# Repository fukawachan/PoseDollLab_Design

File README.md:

# PoseDoll 人偶硬件设计

Manny / Quinn 传感器可动人偶的独立设计仓库。原来位于 `DollSimulation` UE 工程中的硬件、固件与硬件诊断工具已经迁入本目录；UE 插件、角色资产与完整 Python 模拟器留在原项目。

## 当前状态

本次审查同时评估用户新明确的“摆稳后采集、无需实时动捕”场景：[放宽实时指标后的优化任务](Hardware/PoseDoll44/docs/NEXT_REVIEW_STATIC_CAPTURE.zh-CN.md)。Rev O3 当前代码与封存证据保留原时序，低频/触发式架构尚待审查实施。

- **当前推进为 Rev O 第三轮**：[本轮设计、验证与剩余问题](Hardware/PoseDoll44/docs/START_HERE_REVO3.zh-CN.md)。已实现一体板托、外耳钢背摩擦件和磨损状态检查；修正载荷/质量账、时序统计与节点恢复；生成顶入/侧入板件候选。**整机 1.2 kg 已改为非强制偏好**，尺寸、手感和精度要求保留。完整多轴总装与制造门槛尚未闭合。[第三轮审查入口](Hardware/PoseDoll44/docs/REVIEW_REQUEST_REVO3.zh-CN.md)。

- **历史检查点：Rev O 第二轮**：[本轮设计、验证与缺口](Hardware/PoseDoll44/docs/START_HERE_REVO2.zh-CN.md)。已重构 L6 承力/装配、生成 N3/N4 拆板候选并修复入网调度；完整板位、质量目标和物理门槛仍待闭合。**[给 GPT-6 Pro 的第二轮审查说明](Hardware/PoseDoll44/docs/REVIEW_REQUEST_REVO2.zh-CN.md)** 已整理好源码、证据和重点问题。下列 Rev O 审查入口保留为第一轮历史。

- **历史检查点：Rev O Desktop 初轮**：48 cm 为研究锚点，比较 42/45 cm 及较大后备档；已交付双角色布局、三档关节、原生电气布局和七角色固件。板位、预紧和质量预算仍未达标，完整总装尚未完成。
- **约 91 cm 的 Rev M/N1 为备用**：原文件与旧输出保留，以哈希清单冻结。新旧源码、报告和导出分目录保存。
- 第一轮历史入口：[Rev O 当前结果与失败清单](Hardware/PoseDoll44/docs/START_HERE_REVO.zh-CN.md)。
- **第一轮历史独立审查入口：[给 GPT-6 Pro 的审查说明](Hardware/PoseDoll44/docs/REVIEW_REQUEST_REVO.zh-CN.md)**，包含已知失败、证据链接与下一轮修改要求。

以下为备用版的历史基线：

- **机械基线为 Rev N1**：两款分别按 UE 人物参考比例设计，参考身高约 91 cm；胸前大挡板已取消，左肩局部刮碰已修正。
- **下一项为“局部采集 + 外置电源/USB 接口盒”**：方向已确定，新电路板、安装结构和线束尚未实施。
- **小型化仍待比较**：当前尺寸不是已证明的下限，不能直接缩放现有文件，也不能认定重新设计的小型关节必然昂贵。
- 44 个协议槽中，41 轴测量，骨盆 3 轴固定参考；整体位置和全部整体旋转在 UE 调整。
- 当前交付是数字原型候选，尚未实物鉴定。

## 阅读入口

0. [当前主方案 Rev O3](Hardware/PoseDoll44/docs/START_HERE_REVO3.zh-CN.md)；使用 `scripts/run_revo3.py --run-id <唯一编号>` 复跑，`scripts/Start-Viewer.ps1 -Revision revO3` 查看。以下 Rev M/N 文档用于备用版。

1. [最新 Rev N1 设计入口](Hardware/PoseDoll44/START_HERE_REVN.zh-CN.md)
2. [胸部修订与设备外置方案](Hardware/PoseDoll44/docs/CHEST_AND_EXTERNAL_REVN.zh-CN.md)
3. [尺寸、磁铁和关节小型化评估](Hardware/PoseDoll44/docs/SIZE_REVIEW_BEFORE_EXTERNAL.zh-CN.md)
4. [制造说明](Hardware/PoseDoll44/docs/FABRICATION_REVM.zh-CN.md)、[装配说明](Hardware/PoseDoll44/docs/ASSEMBLY_REVM.zh-CN.md)、[测试和校准](Hardware/PoseDoll44/docs/BUILD_AND_CALIBRATE_REVM.zh-CN.md)
5. [迁移记录和验证](docs/MIGRATION.zh-CN.md)

Rev M 文档描述原完整基线，使用时应应用 Rev N1 的取消件和左肩修订。更早版本与 `planning/` 是历史依据，不能混作当前制造说明。

## 目录组织

| 路径 | 用途 |
|---|---|
| `Hardware/PoseDoll44/cad/` | 参数化机械模型，保留当前模型仍引用的历史模块 |
| `Hardware/PoseDoll44/electronics/` | 原生 KiCad 工程、符号/封装及板级 STEP 输入 |
| `Hardware/PoseDoll44/mechanical_manifest/` | 轴、接口、比例和网络定义 |
| `Hardware/PoseDoll44/docs/`、`verification/` | 设计说明、数字检查和原型验收依据 |
| `Hardware/PoseDoll44/generated/` | 总装、打印件、查看器、交付清单和本地 CAD 缓存 |
| `Hardware/PoseDoll44/reference/`、`references/` | UE 参考数据及元件资料 |
| `Hardware/PoseDoll44/harness/` | 两款线束与下料表 |
| `Firmware/PoseDollFullBody/` | 六节点完整固件与主机端 C 核心测试 |
| `Firmware/PoseDollHardware/` | 早期单关节固件，历史用途 |
| `Tools/PoseDollHardwareBridge/` | 诊断、校准、数据转换和测试 |
| `Tools/PoseDollSimulator/`、`Shared/` | 硬件需要的协议/运动学代码及配置快照，不含模拟器 GUI |
| `planning/` | 原始规划包副本，父目录中的原下载包也保留 |
| `scripts/` | 独立仓库的检查、构建和查看器入口 |
| `.local/` | 本机迁移清单、运行结果等，不入 Git |

保留 `Hardware/`、`Firmware/`、`Tools/` 层级，以保持已有相对路径及历史资料的可追溯性。协议快照来源与逐文件哈希见 [software_snapshot.json](docs/software_snapshot.json)。

## 环境与离线检查

在本目录打开 PowerShell。本机已经建立独立 `.venv`；新克隆可执行：

```powershell
py -3.13 -m venv .venv
.\.venv\Scripts\python.exe -m pip install -r requirements.txt
.\.venv\Scripts\python.exe scripts/check_repository.py
.\scripts\Build-Design.ps1 -Stage OfflineTests
```

离线检查包括协议配置、Python 测试、C 核心测试和 C/Python 数据帧一致性；不连接硬件或操作 UE。C 测试需要 Visual Studio C 工具链，`-VcVars` 可指定 `vcvars64.bat`。本机迁移后结果为 **81 个 Python 测试、9 个 C 场景通过，数据帧逐字节一致**。

## 打开三维查看器

```powershell
.\scripts\Start-Viewer.ps1
```

默认根据 `verification/revO3/latest.json` 打开 Rev O3 查看器，当前为 `http://127.0.0.1:8874/generated/revO3/runs/o3_20260924_r3/review.html`；通过 `-Revision revN` 打开 91 cm 备用版，仅绑定本机。`-NoBrowser` 只启动服务；端口冲突时可用 `-Port` 指定另一端口，不会自动终止其他进程。

Rev O3 的当前及历史检查运行、HTML、网格、STEP、原生 KiCad 板件、固件产物与原始日志随本次审查提交收录；宿主 C 编译产物通过逐件哈希的 portable ZIP 保存。Rev O 第一轮的 HTML、轻量网格、布局数据及三档关节 STEP 也保留。十份体型布局 STEP 下载需先用 `Build-RevO.ps1 -Stage CAD` 重建。91 cm 备用查看器仍依赖未纳入 Git 的大型网格，需复制旧输出或重建。

## CAD、电路和固件

- CAD：CadQuery 2.7。现有 `Hardware/PoseDoll44/tools/run_cad.py` 可使用本机 CQ-editor 2.7 的环境，需要 CQ-editor 保持开启、Python 版本匹配；也可自行安装常规 CadQuery 环境。
- 电路：KiCad 10，打开 `electronics/` 中对应 `.kicad_pro`。搬迁前已打开的 CQ-editor/KiCad 文件，应从新目录重新打开，避免保存回原路径。
- 固件：ESP-IDF 6.1、ESP32-S3。旧构建缓存已保留，但含旧绝对路径；不要直接在其中增量构建。
- 布线工具：Freerouting 2.4.1 JAR 保留在本机 `Hardware/PoseDoll44/tools/vendor/`，不入 Git；许可证与说明保留。

```powershell
.\scripts\Build-Design.ps1 -Stage CAD
.\scripts\Build-Design.ps1 -Stage Firmware
```

CAD 阶段生成/复核 Rev M 完整基线，耗时较长。Rev N1 的修订脚本位于 `cad/revN/`，依赖 Rev M 完整输出及其复核结果，不是上述命令自动生成的另一套角色。当前源码与必要 CAD 输入纳入 Git。

新构建入口使用本仓库 `.venv`。Firmware 阶段会把检测到旧工程路径的节点缓存移入 `.local/legacy-firmware-builds/` 后重新构建，不删除缓存、不烧录。旧脚本中的 CQ-editor、KiCad、ESP-IDF 安装盘符仍是本机配置；换电脑须配置工具路径，历史工具可参考 `local_toolchain.example.json`。UE 参考重新导出需要原 UE 工程及插件，但导出脚本现在将数据写到本设计仓库。

## Git 与本地成果

Git 收录设计源码、KiCad 工程、固件、必要板级 STEP/角色参考输入、协议快照、说明、交付元数据和检查记录。`.gitattributes` 保留原行尾，避免检出时破坏来源文件的字节哈希。

大型总装 STEP、查看器大网格、CAD 缓存、ESP-IDF 构建目录、Python 环境和第三方工具二进制保留在磁盘，由 `.gitignore` 排除；没有启用 Git LFS。Rev O 审查快照额外收录三档单关节总成 STEP、两个 A 级配合样片 STEP/STL、轻量查看器与本轮原始编译/ERC/DRC 日志，Rev O3 本次另显式收录三个检查运行及其可追溯产物，仍未放开其他版本的整个生成目录。其他机器如需完整本地成果，应另外复制 `Hardware/PoseDoll44/generated/`。**推送 Git 不等于备份全部 6.87 GB 本地成果。**

现有验证报告保留为历史快照，迁移后的路径修复和检查另列记录；没有把迁移当成新一轮全身工程验证。本轮提交由使用者推送到远端；审查应指定 `design/revO-desktop-external` 分支和所读取的完整提交号。

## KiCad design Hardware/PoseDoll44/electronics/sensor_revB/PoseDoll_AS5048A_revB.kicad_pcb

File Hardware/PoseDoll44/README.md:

# PoseDoll Manny / Quinn hardware design

[Repository README](../../README.md) · [Rev N1 entry](START_HERE_REVN.zh-CN.md) · [Size review](docs/SIZE_REVIEW_BEFORE_EXTERNAL.zh-CN.md)

Current mechanical candidate: Rev N1 (Rev M full body, chest facade removed, left shoulder clearance corrected). Rear electronics remain integrated; local acquisition plus an external interface box is authorized but not implemented. Miniaturization feasibility and cost are unresolved.

CAD source: `cad/revM/final_model.py` plus `cad/revN/chest_clearance.py`. Historical revisions remain because current code and input provenance refer to them. Use revision manifests rather than mixing standalone exports.

This is a digital prototype candidate, not a manufacturing release or a physically qualified product. See the repository README for the migrated layout, toolchain, ignored local exports, offline checks and viewer startup.

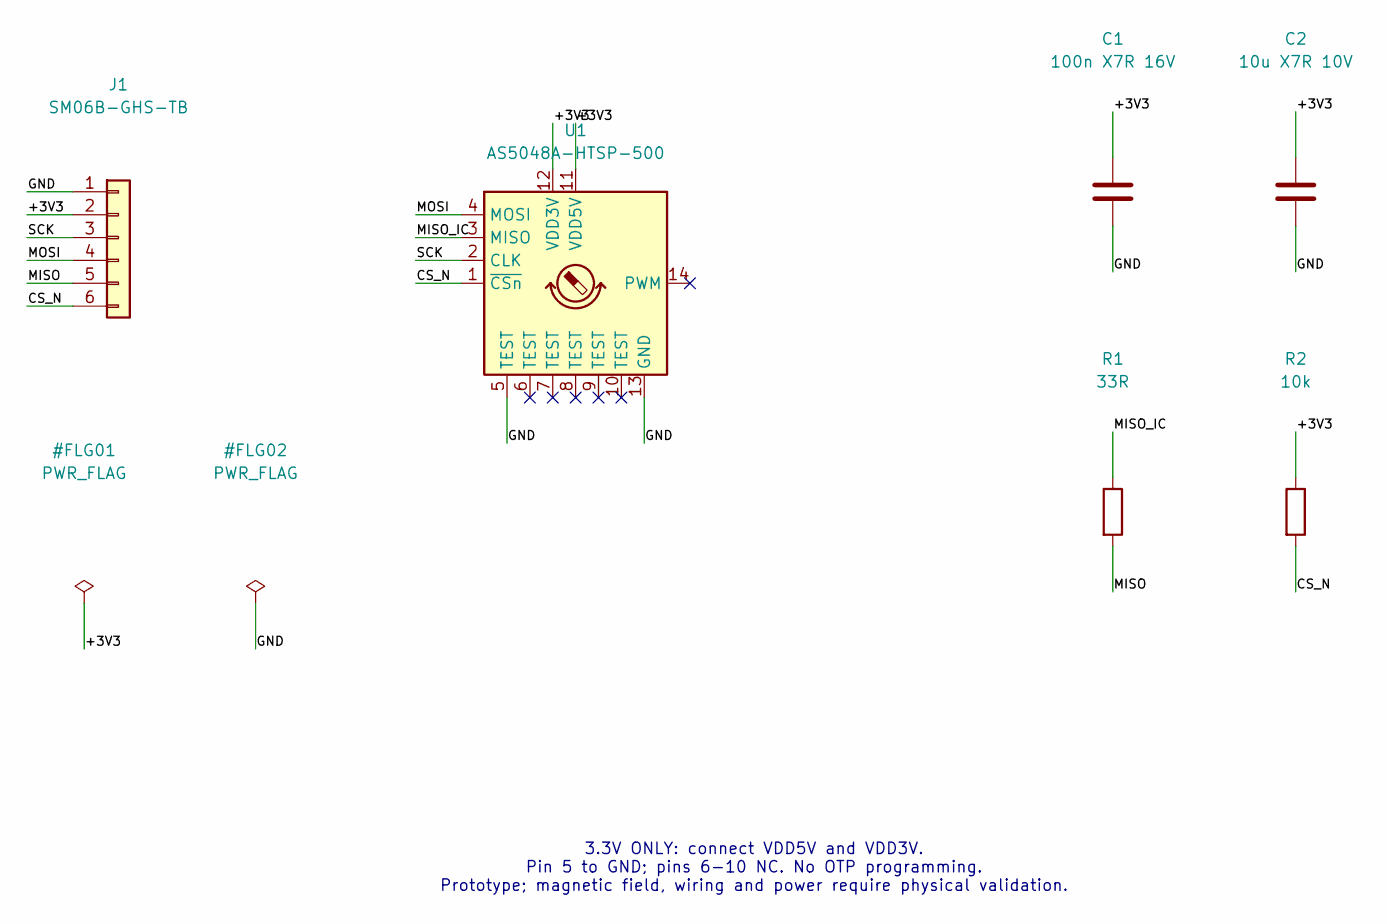
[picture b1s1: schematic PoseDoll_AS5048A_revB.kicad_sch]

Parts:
C1: 100n X7R 16V; C_0603_1608Metric
C2: 10u X7R 10V; C_0805_2012Metric
J1: SM06B-GHS-TB; JST_GH_SM06B-GHS-TB_1x06-1MP_P1.25mm_Horizontal
R1: 33R; R_0603_1608Metric
R2: 10k; R_0603_1608Metric
U1: AS5048A-HTSP-500; TSSOP-14_4.4x5mm_P0.65mm

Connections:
/+3V3: C1.1, C2.1, J1.2, R2.1, U1.11 (VDD5V), U1.12 (VDD3V)
/CS_N: J1.6, R2.2, U1.1 (~CSn)
/GND: C1.2, C2.2, J1.1, U1.5 (TEST), U1.13 (GND)
/MISO: J1.5, R1.2
/MISO_IC: R1.1, U1.3 (MISO)
/MOSI: J1.4, U1.4 (MOSI)
/SCK: J1.3, U1.2 (CLK)

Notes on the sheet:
3.3V ONLY: connect VDD5V and VDD3V. Pin 5 to GND; pins 6-10 NC. No OTP programming. Prototype; magnetic field, wiring and power require physical validation.

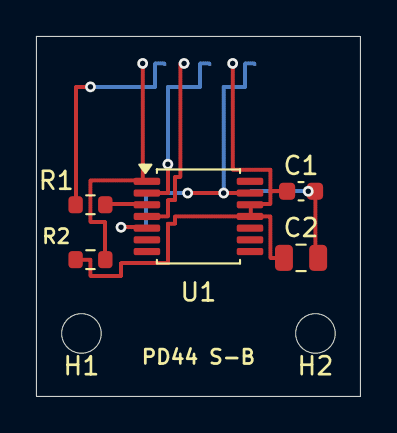
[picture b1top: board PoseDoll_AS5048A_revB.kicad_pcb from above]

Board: 2 copper layers, 18.0 x 20.0 mm, 8 parts (1 on the bottom side), 7 nets.

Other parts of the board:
H1, H2: MountingHole_2.2mm_M2

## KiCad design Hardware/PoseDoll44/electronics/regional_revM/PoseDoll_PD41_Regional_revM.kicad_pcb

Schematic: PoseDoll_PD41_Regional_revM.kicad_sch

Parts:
C1: 10u X5R 25V / CL21A106KAYNNNE; C_0805_2012Metric
C2, C4: 22u X5R 16V / CL21A226MOYNNNE; C_0805_2012Metric
C3, C5, C7, C8, C21, C22, C23, C24, C25, C26, C27, C28, C29: 100n X7R; C_0603_1608Metric
C6: 1u X7R; C_0603_1608Metric
D1: PESD5V0S2BT,215; SOT-23
D2: TPD2E2U06DCKR; SOT-323_SC-70
J1: 5V from fused pelvis star; JST_PH_B2B-PH-SM4-TB_1x02-1MP_P2.00mm_Vertical
J2: CAN IN / GND-L-H; JST_GH_BM03B-GHS-TBT_1x03-1MP_P1.25mm_Vertical
J3: CAN OUT / GND-L-H; JST_GH_BM03B-GHS-TBT_1x03-1MP_P1.25mm_Vertical
J4: USB data only; external 5V required; USB_C_Data_Port
J11: P1 sensor / CS GPIO2; JST_SH_BM06B-SRSS-TB_1x06-1MP_P1.00mm_Vertical
J12: P2 sensor / CS GPIO4; JST_SH_BM06B-SRSS-TB_1x06-1MP_P1.00mm_Vertical
J13: P3 sensor / CS GPIO5; JST_SH_BM06B-SRSS-TB_1x06-1MP_P1.00mm_Vertical
J14: P4 sensor / CS GPIO6; JST_SH_BM06B-SRSS-TB_1x06-1MP_P1.00mm_Vertical
J15: P5 sensor / CS GPIO7; JST_SH_BM06B-SRSS-TB_1x06-1MP_P1.00mm_Vertical
J16: P6 sensor / CS GPIO8; JST_SH_BM06B-SRSS-TB_1x06-1MP_P1.00mm_Vertical
J17: P7 sensor / CS GPIO9; JST_SH_BM06B-SRSS-TB_1x06-1MP_P1.00mm_Vertical
J18: P8 sensor / CS GPIO10; JST_SH_BM06B-SRSS-TB_1x06-1MP_P1.00mm_Vertical
J19: P9 sensor / CS GPIO14; JST_SH_BM06B-SRSS-TB_1x06-1MP_P1.00mm_Vertical
JP1: CAN TERM: close endpoints only; PinHeader_1x02_P2.00mm_Vertical
L1: LSXND4040TKL2R2MDG / 2.2uH; L_Taiyo-Yuden_NR-40xx
Q1: MMBT3904; SOT-23
R1, R2, R4, R113, R117, R123, R127, R133, R137, R143, R147, R153, R157, R163, R167, R173, R177, R183, R187, R193, R197: 10k; R_0603_1608Metric
R3, R6, R7, R8, R116, R126, R136, R146, R156, R166, R176, R186, R196: 100k; R_0603_1608Metric
R5: 120R 1% 0.33W / CRCW0603120RFKEAHP; R_0603_1608Metric
R9, R10: 5.1k 1%; R_0603_1608Metric
R11, R12: 22R; R_0603_1608Metric
R110, R111, R112, R120, R121, R122, R130, R131, R132, R140, R141, R142, R150, R151, R152, R160, R161, R162, R170, R171, R172, R180, R181, R182, R190, R191, R192: 100R; R_0603_1608Metric
R114, R115, R124, R125, R134, R135, R144, R145, R154, R155, R164, R165, R174, R175, R184, R185, R194, R195: 47k; R_0603_1608Metric
SW1: RESET; SW_SPST_TL3305A
SW2: BOOT; SW_SPST_TL3305A
TP1: UART_TX; TestPoint_Pad_D1.0mm
TP2: UART_RX; TestPoint_Pad_D1.0mm
TP3: GND; TestPoint_Pad_D1.0mm
TP4: PG; TestPoint_Pad_D1.0mm
U1: ESP32-S3-WROOM-1-N8; ESP32-S3-WROOM-1
U2: TPS62162DSGR; Texas_DSG0008A_WSON-8-1EP_2x2mm_P0.5mm_EP0.9x1.6mm
U3: TCAN332DR; SOIC-8_3.9x4.9mm_P1.27mm
U4: TS3USB221ERSER; Texas_UQFN-10_1.5x2mm_P0.5mm
U11, U12, U13, U14, U15, U16, U17, U18, U19: SN74LVC125APWR; TSSOP-14_4.4x5mm_P0.65mm

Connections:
/+3V3: C2.1, C4.1, C5.1, C7.1, C8.1, C21.1, C22.1, C23.1, C24.1, C25.1, C26.1, C27.1, C28.1, C29.1, J11.2, J12.2, J13.2, J14.2, J15.2, J16.2, J17.2, J18.2, J19.2, L1.2, R1.1, R2.1, R3.1, R4.1, R8.1, R113.1, R117.1, R123.1, R127.1, R133.1, R137.1, R143.1, R147.1, R153.1, R157.1, R163.1, R167.1, R173.1, R177.1, R183.1, R187.1, R193.1, R197.1, U1.2 (3V3), U2.6 (VOS), U3.3 (VCC), U4.10 (VCC), U11.14 (VCC), U12.14 (VCC), U13.14 (VCC), U14.14 (VCC), U15.14 (VCC), U16.14 (VCC), U17.14 (VCC), U18.14 (VCC), U19.14 (VCC)
/+5V_IN: C1.1, C3.1, J1.1, U2.2 (VIN), U2.3 (EN)
/BOOT_N: R2.2, SW2.1, U1.27 (IO0)
/CAN_H: D1.2 (CAN2), J2.3, J3.3, R5.1, U3.7 (CANH)
/CAN_L: D1.1 (CAN1), J2.2, J3.2, JP1.2 (B), U3.6 (CANL)
/CAN_RX: U1.11 (IO18), U3.4 (RXD)
/CAN_TX: R4.2, U1.10 (IO17), U3.1 (TXD)
/CC1: J4.A5 (CC1), R9.1
/CC2: J4.B5 (CC2), R10.1
/CS1_MCU: R113.2, U1.38 (IO2), U11.1 (1OE_N), U11.4 (2OE_N), U11.10 (3OE_N), U11.12 (4A)
/CS2_MCU: R123.2, U1.4 (IO4), U12.1 (1OE_N), U12.4 (2OE_N), U12.10 (3OE_N), U12.12 (4A)
/CS3_MCU: R133.2, U1.5 (IO5), U13.1 (1OE_N), U13.4 (2OE_N), U13.10 (3OE_N), U13.12 (4A)
/CS4_MCU: R143.2, U1.6 (IO6), U14.1 (1OE_N), U14.4 (2OE_N), U14.10 (3OE_N), U14.12 (4A)
/CS5_MCU: R153.2, U1.7 (IO7), U15.1 (1OE_N), U15.4 (2OE_N), U15.10 (3OE_N), U15.12 (4A)
/CS6_MCU: R163.2, U1.12 (IO8), U16.1 (1OE_N), U16.4 (2OE_N), U16.10 (3OE_N), U16.12 (4A)
/CS7_MCU: R173.2, U1.17 (IO9), U17.1 (1OE_N), U17.4 (2OE_N), U17.10 (3OE_N), U17.12 (4A)
/CS8_MCU: R183.2, U1.18 (IO10), U18.1 (1OE_N), U18.4 (2OE_N), U18.10 (3OE_N), U18.12 (4A)
/CS9_MCU: R193.2, U1.22 (IO14), U19.1 (1OE_N), U19.4 (2OE_N), U19.10 (3OE_N), U19.12 (4A)
/EN: C6.1, R1.2, SW1.1, U1.3 (EN)
/GND: C1.2, C2.2, C3.2, C4.2, C5.2, C6.2, C7.2, C8.2, C21.2, C22.2, C23.2, C24.2, C25.2, C26.2, C27.2, C28.2, C29.2, D1.3 (GND), D2.3, J1.2, J2.1, J3.1, J4.A1 (GND), J4.A12 (GND), J4.B1 (GND), J4.B12 (GND), J4.SH (SHIELD), J11.1, J12.1, J13.1, J14.1, J15.1, J16.1, J17.1, J18.1, J19.1, Q1.2 (E), R7.2, R9.2, R10.2, R114.2, R115.2, R116.2, R124.2, R125.2, R126.2, R134.2, R135.2, R136.2, R144.2, R145.2, R146.2, R154.2, R155.2, R156.2, R164.2, R165.2, R166.2, R174.2, R175.2, R176.2, R184.2, R185.2, R186.2, R194.2, R195.2, R196.2, SW1.2, SW2.2, TP3.1, U1.1 (GND), U1.40 (GND), U1.41 (GND), U2.1 (PGND), U2.4 (AGND), U2.5 (FB), U2.9 (PAD), U3.2 (GND), U4.5 (GND), U4.9 (S), U11.7 (GND), U11.13 (4OE_N), U12.7 (GND), U12.13 (4OE_N), U13.7 (GND), U13.13 (4OE_N), U14.7 (GND), U14.13 (4OE_N), U15.7 (GND), U15.13 (4OE_N), U16.7 (GND), U16.13 (4OE_N), U17.7 (GND), U17.13 (4OE_N), U18.7 (GND), U18.13 (4OE_N), U19.7 (GND), U19.13 (4OE_N)
/P1_CS: J11.6, R112.2, R117.2
/P1_CS_DRV: R112.1, U11.11 (4Y)
/P1_MISO: J11.5, R116.1, U11.9 (3A)
/P1_MOSI: J11.4, R111.2, R115.1
/P1_MOSI_DRV: R111.1, U11.6 (2Y)
/P1_SCK: J11.3, R110.2, R114.1
/P1_SCK_DRV: R110.1, U11.3 (1Y)
/P2_CS: J12.6, R122.2, R127.2
/P2_CS_DRV: R122.1, U12.11 (4Y)
/P2_MISO: J12.5, R126.1, U12.9 (3A)
/P2_MOSI: J12.4, R121.2, R125.1
/P2_MOSI_DRV: R121.1, U12.6 (2Y)
/P2_SCK: J12.3, R120.2, R124.1
/P2_SCK_DRV: R120.1, U12.3 (1Y)
/P3_CS: J13.6, R132.2, R137.2
/P3_CS_DRV: R132.1, U13.11 (4Y)
/P3_MISO: J13.5, R136.1, U13.9 (3A)
/P3_MOSI: J13.4, R131.2, R135.1
/P3_MOSI_DRV: R131.1, U13.6 (2Y)
/P3_SCK: J13.3, R130.2, R134.1
/P3_SCK_DRV: R130.1, U13.3 (1Y)
/P4_CS: J14.6, R142.2, R147.2
/P4_CS_DRV: R142.1, U14.11 (4Y)
/P4_MISO: J14.5, R146.1, U14.9 (3A)
/P4_MOSI: J14.4, R141.2, R145.1
/P4_MOSI_DRV: R141.1, U14.6 (2Y)
/P4_SCK: J14.3, R140.2, R144.1
/P4_SCK_DRV: R140.1, U14.3 (1Y)
/P5_CS: J15.6, R152.2, R157.2
/P5_CS_DRV: R152.1, U15.11 (4Y)
/P5_MISO: J15.5, R156.1, U15.9 (3A)
/P5_MOSI: J15.4, R151.2, R155.1
/P5_MOSI_DRV: R151.1, U15.6 (2Y)
/P5_SCK: J15.3, R150.2, R154.1
/P5_SCK_DRV: R150.1, U15.3 (1Y)
/P6_CS: J16.6, R162.2, R167.2
/P6_CS_DRV: R162.1, U16.11 (4Y)
/P6_MISO: J16.5, R166.1, U16.9 (3A)
/P6_MOSI: J16.4, R161.2, R165.1
/P6_MOSI_DRV: R161.1, U16.6 (2Y)
/P6_SCK: J16.3, R160.2, R164.1
/P6_SCK_DRV: R160.1, U16.3 (1Y)
/P7_CS: J17.6, R172.2, R177.2
/P7_CS_DRV: R172.1, U17.11 (4Y)
/P7_MISO: J17.5, R176.1, U17.9 (3A)
/P7_MOSI: J17.4, R171.2, R175.1
/P7_MOSI_DRV: R171.1, U17.6 (2Y)
/P7_SCK: J17.3, R170.2, R174.1
/P7_SCK_DRV: R170.1, U17.3 (1Y)
/P8_CS: J18.6, R182.2, R187.2
/P8_CS_DRV: R182.1, U18.11 (4Y)
/P8_MISO: J18.5, R186.1, U18.9 (3A)
/P8_MOSI: J18.4, R181.2, R185.1
/P8_MOSI_DRV: R181.1, U18.6 (2Y)
/P8_SCK: J18.3, R180.2, R184.1
/P8_SCK_DRV: R180.1, U18.3 (1Y)
/P9_CS: J19.6, R192.2, R197.2
/P9_CS_DRV: R192.1, U19.11 (4Y)
/P9_MISO: J19.5, R196.1, U19.9 (3A)
/P9_MOSI: J19.4, R191.2, R195.1
/P9_MOSI_DRV: R191.1, U19.6 (2Y)
/P9_SCK: J19.3, R190.2, R194.1
/P9_SCK_DRV: R190.1, U19.3 (1Y)
/PG: R3.2, TP4.1, U2.8 (PG)
/SPI_MISO: U1.21 (IO13), U11.8 (3Y), U12.8 (3Y), U13.8 (3Y), U14.8 (3Y), U15.8 (3Y), U16.8 (3Y), U17.8 (3Y), U18.8 (3Y), U19.8 (3Y)
/SPI_MOSI: U1.19 (IO11), U11.5 (2A), U12.5 (2A), U13.5 (2A), U14.5 (2A), U15.5 (2A), U16.5 (2A), U17.5 (2A), U18.5 (2A), U19.5 (2A)
/SPI_SCK: U1.20 (IO12), U11.2 (1A), U12.2 (1A), U13.2 (1A), U14.2 (1A), U15.2 (1A), U16.2 (1A), U17.2 (1A), U18.2 (1A), U19.2 (1A)
/SW_BUCK: L1.1, U2.7 (SW)
/TERM_R: JP1.1 (A), R5.2
/UART_RX: TP2.1, U1.36 (RXD0)
/UART_TX: TP1.1, U1.37 (TXD0)
/USB_DM_HOST: D2.2, J4.A7 (D-), J4.B7 (D-), U4.7 (D-)
/USB_DM_IC: R12.2, U1.13 (USB_D-)
/USB_DM_SW: R12.1, U4.2 (1D-)
/USB_DP_HOST: D2.1, J4.A6 (D+), J4.B6 (D+), U4.8 (D+)
/USB_DP_IC: R11.2, U1.14 (USB_D+)
/USB_DP_SW: R11.1, U4.1 (1D+)
/USB_OE_N: Q1.3 (C), R8.2, U4.6 (OE_N)
/VBUS_BASE: Q1.1 (B), R6.2, R7.1
/VBUS_USB: J4.A4 (VBUS), J4.A9 (VBUS), J4.B4 (VBUS), J4.B9 (VBUS), R6.1

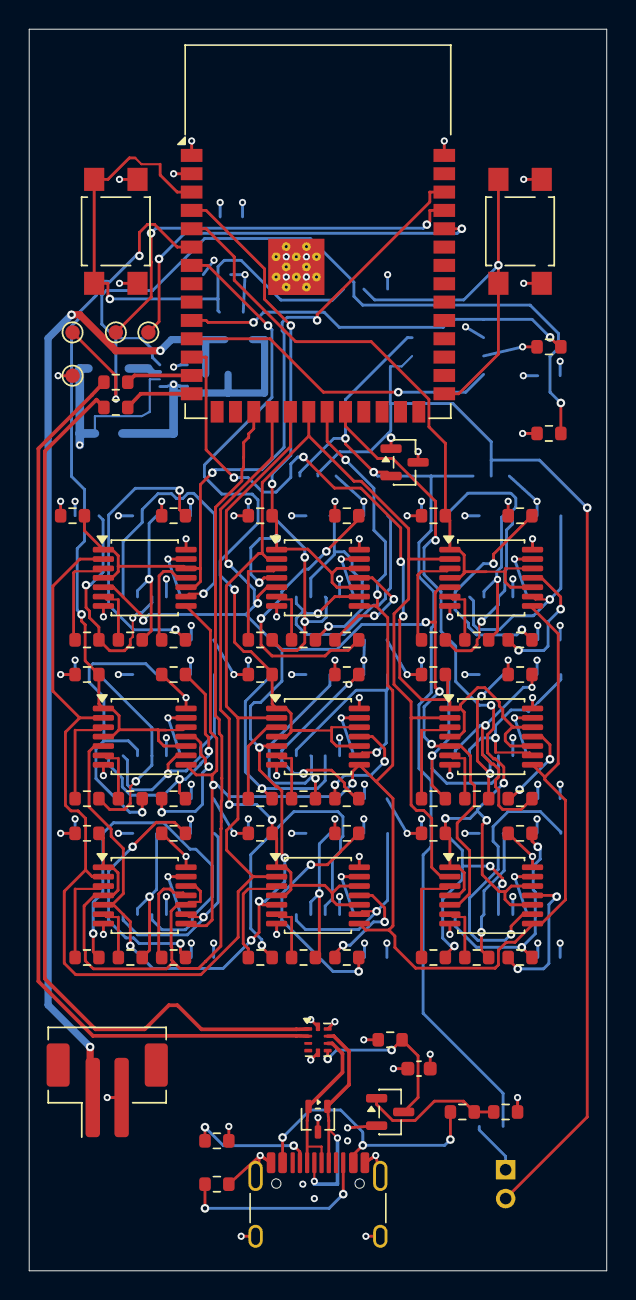
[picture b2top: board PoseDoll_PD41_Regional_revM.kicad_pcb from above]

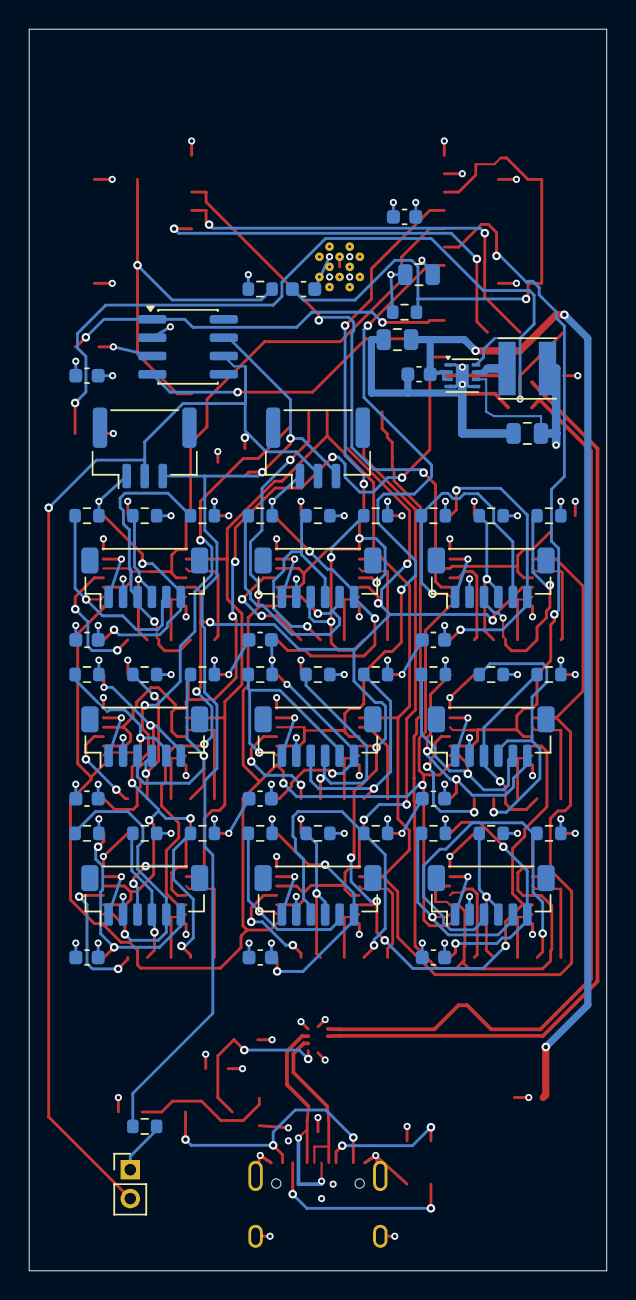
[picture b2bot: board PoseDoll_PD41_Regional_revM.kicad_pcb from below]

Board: 4 copper layers, 40.0 x 86.0 mm, 138 parts (61 on the bottom side), 100 nets.

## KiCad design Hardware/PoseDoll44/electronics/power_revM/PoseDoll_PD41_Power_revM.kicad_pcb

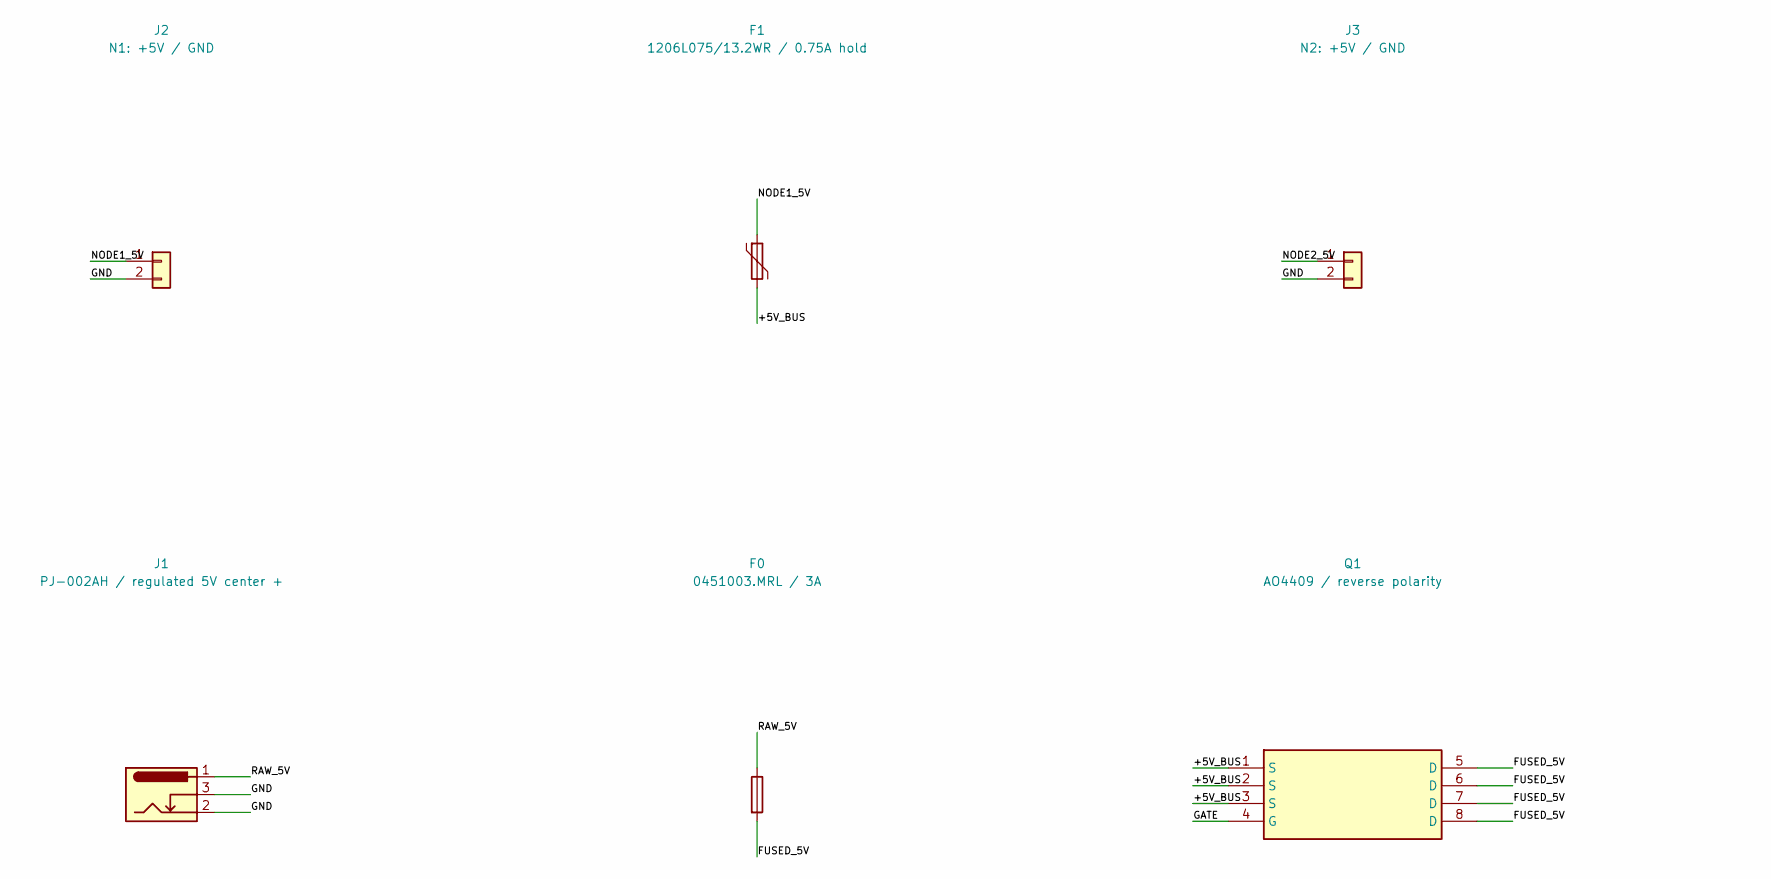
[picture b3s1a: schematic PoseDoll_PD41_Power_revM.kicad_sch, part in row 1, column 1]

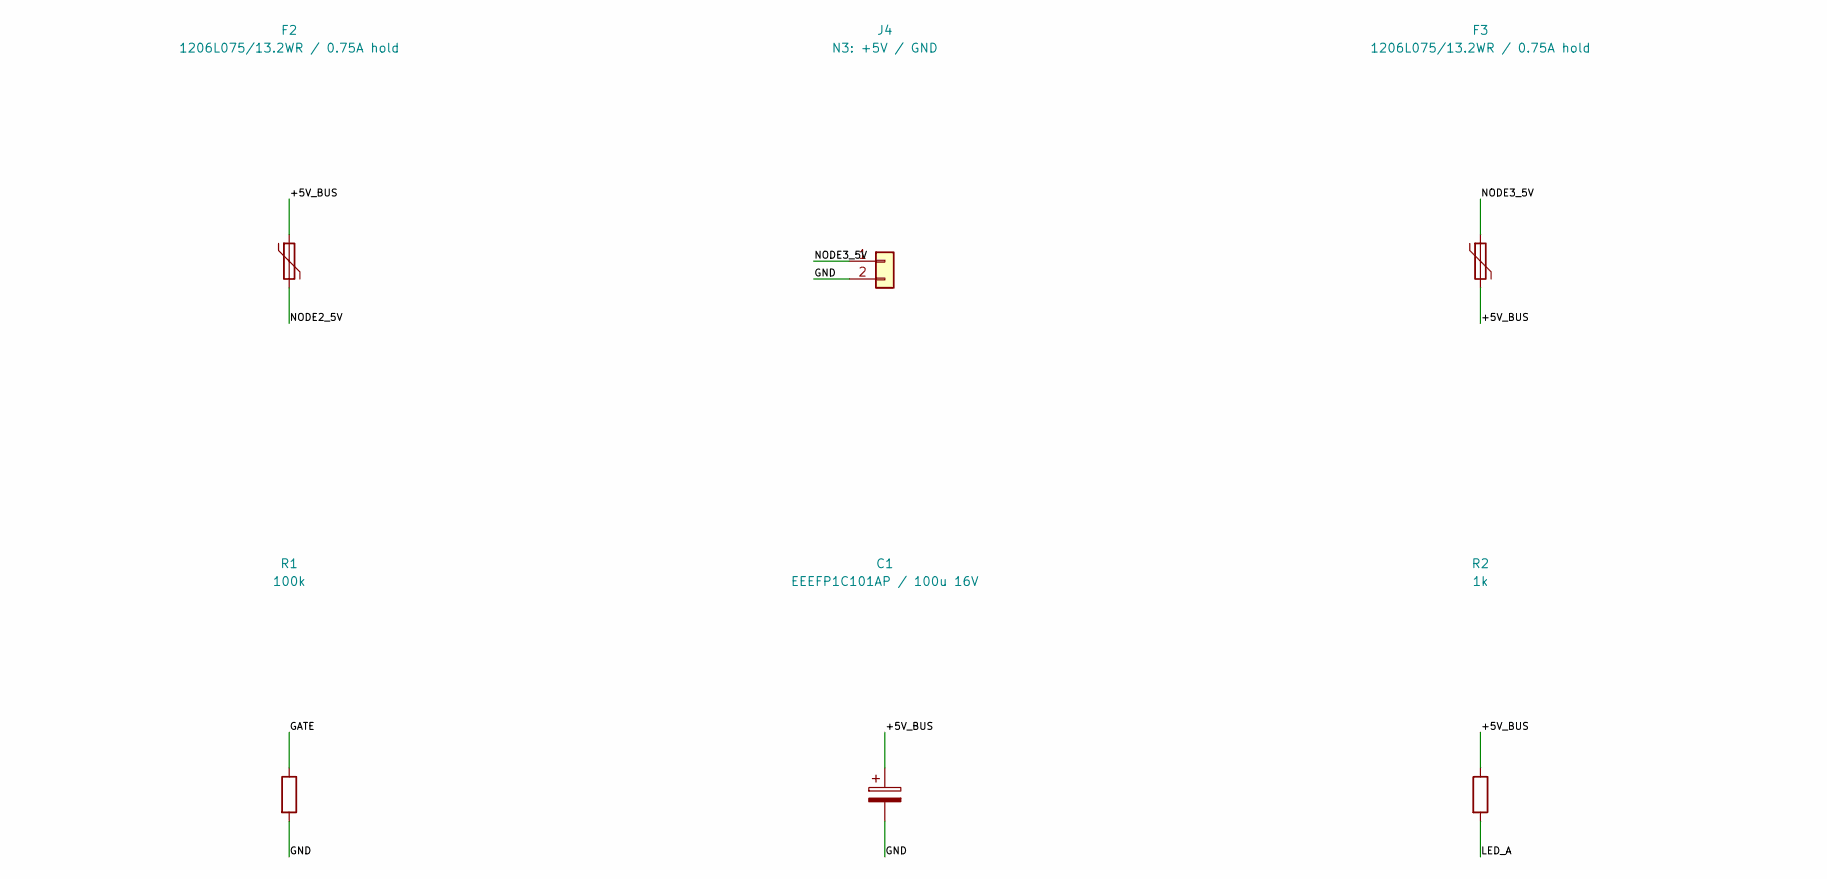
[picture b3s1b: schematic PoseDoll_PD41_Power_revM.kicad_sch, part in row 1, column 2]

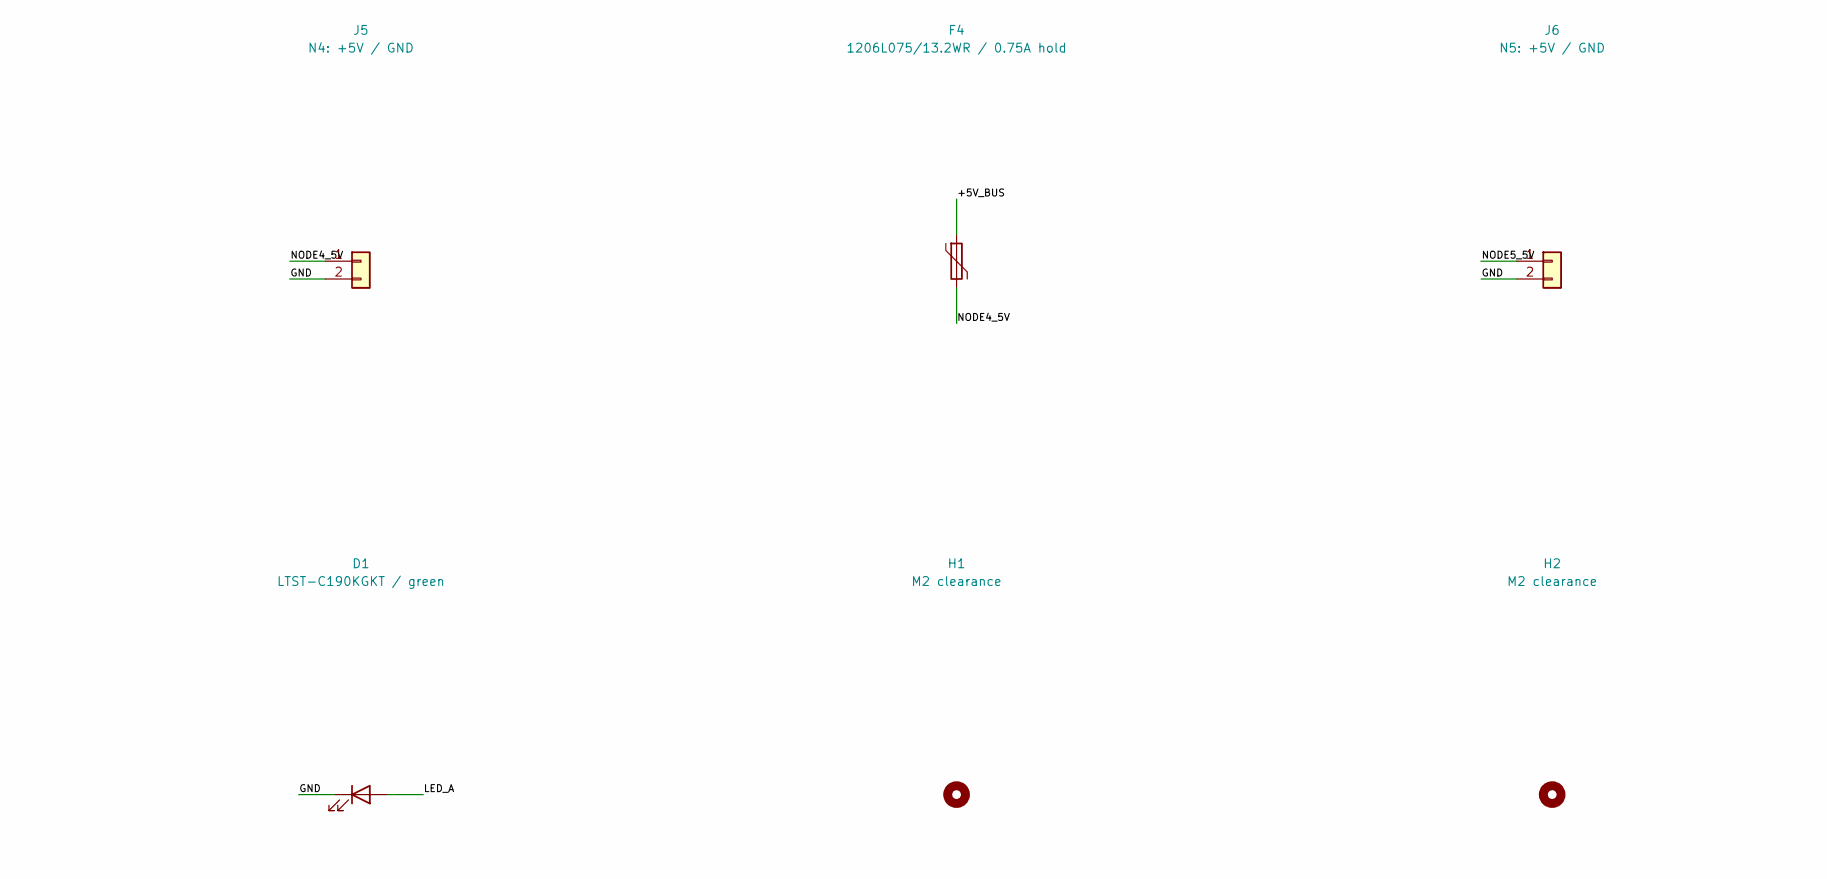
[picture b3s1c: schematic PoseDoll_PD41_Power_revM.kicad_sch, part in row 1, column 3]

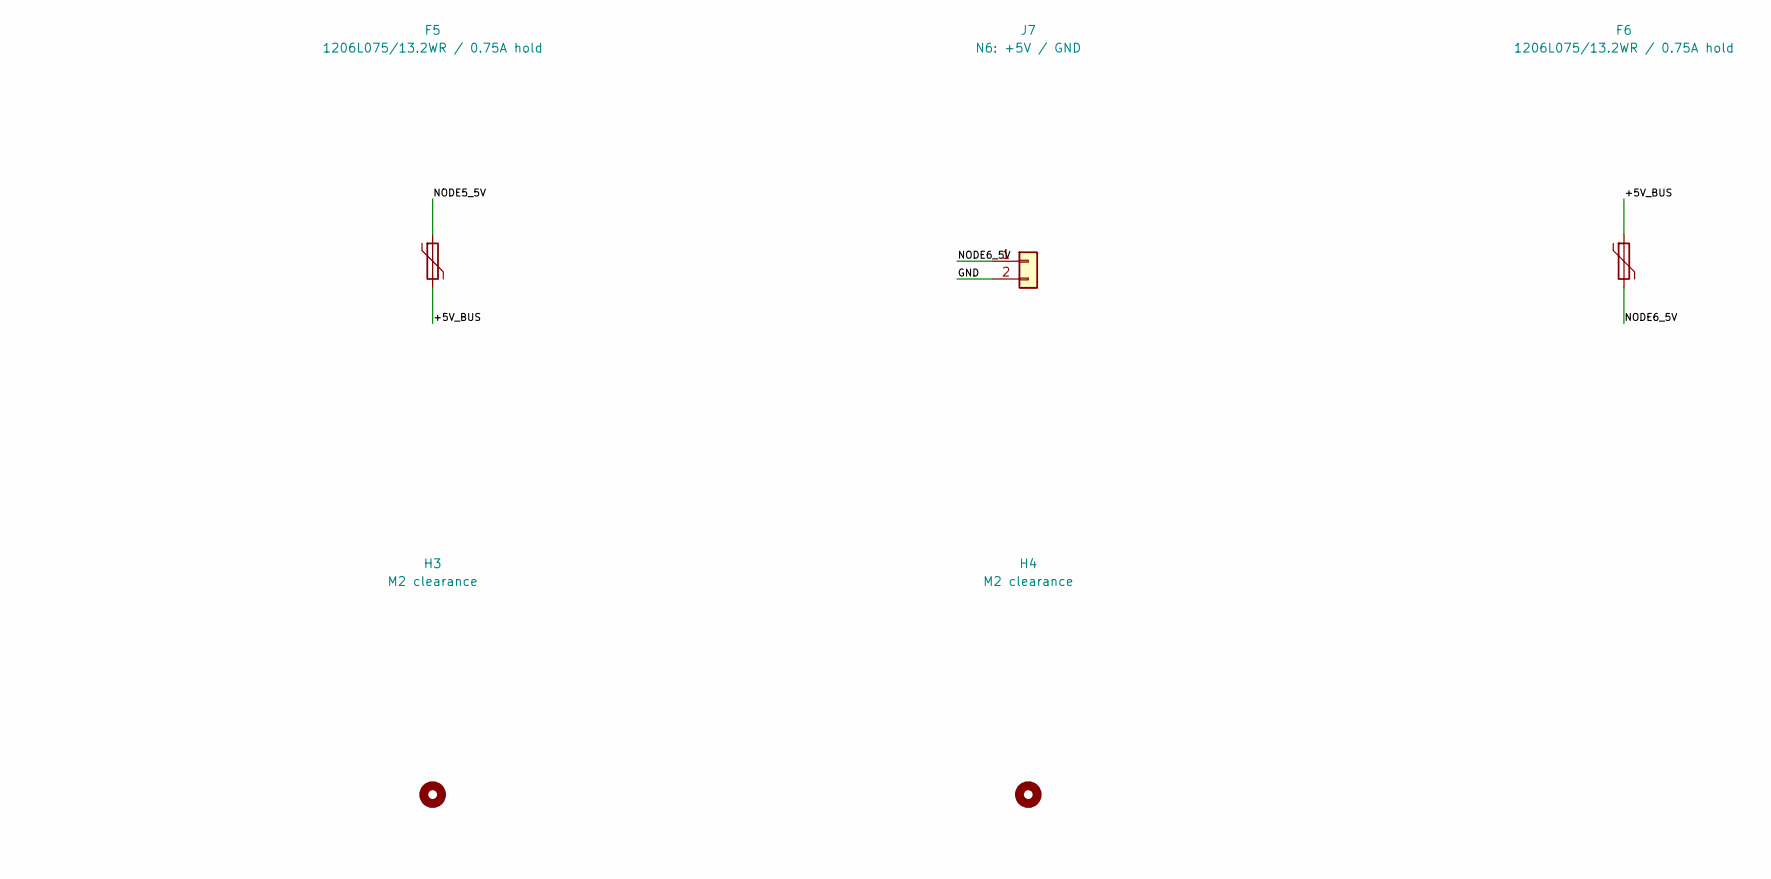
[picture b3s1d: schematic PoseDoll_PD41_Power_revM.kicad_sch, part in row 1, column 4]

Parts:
C1: EEEFP1C101AP / 100u 16V; CP_Elec_6.3x5.8
D1: LTST-C190KGKT / green; LED_0603_1608Metric
F0: 0451003.MRL / 3A; Fuse_Littelfuse-NANO2-451_453
F1, F2, F3, F4, F5, F6: 1206L075/13.2WR / 0.75A hold; Fuse_1206_3216Metric
H1, H2, H3, H4: M2 clearance; MountingHole_2.2mm_M2
J1: PJ-002AH / regulated 5V center +; PJ_002AH_verified
J2: N1: +5V / GND; JST_PH_B2B-PH-K_1x02_P2.00mm_Vertical
J3: N2: +5V / GND; JST_PH_B2B-PH-K_1x02_P2.00mm_Vertical
J4: N3: +5V / GND; JST_PH_B2B-PH-K_1x02_P2.00mm_Vertical
J5: N4: +5V / GND; JST_PH_B2B-PH-K_1x02_P2.00mm_Vertical
J6: N5: +5V / GND; JST_PH_B2B-PH-K_1x02_P2.00mm_Vertical
J7: N6: +5V / GND; JST_PH_B2B-PH-K_1x02_P2.00mm_Vertical
Q1: AO4409 / reverse polarity; SOIC-8_3.9x4.9mm_P1.27mm
R1: 100k; R_0603_1608Metric
R2: 1k; R_0603_1608Metric

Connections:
/+5V_BUS: C1.1, F1.2, F2.1, F3.2, F4.1, F5.2, F6.1, Q1.1 (S), Q1.2 (S), Q1.3 (S), R2.1
/FUSED_5V: F0.2, Q1.5 (D), Q1.6 (D), Q1.7 (D), Q1.8 (D)
/GATE: Q1.4 (G), R1.1
/GND: C1.2, D1.1 (K), J1.2, J1.3, J2.2, J3.2, J4.2, J5.2, J6.2, J7.2, R1.2
/LED_A: D1.2 (A), R2.2
/NODE1_5V: F1.1, J2.1
/NODE2_5V: F2.2, J3.1
/NODE3_5V: F3.1, J4.1
/NODE4_5V: F4.2, J5.1
/NODE5_5V: F5.1, J6.1
/NODE6_5V: F6.2, J7.1
/RAW_5V: F0.1, J1.1

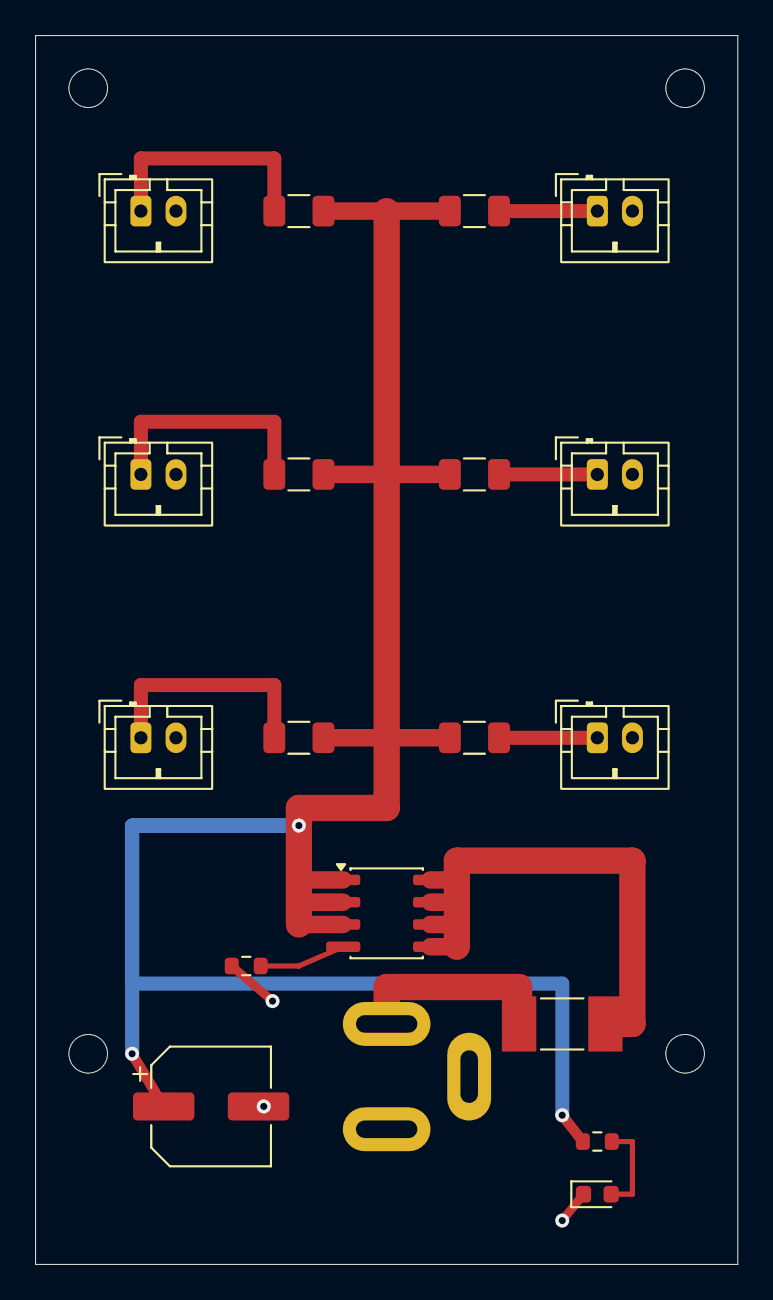
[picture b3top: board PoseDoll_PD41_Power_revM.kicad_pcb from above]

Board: 2 copper layers, 40.0 x 70.0 mm, 23 parts (0 on the bottom side), 12 nets.
